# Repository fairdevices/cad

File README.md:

# Faidevices CAD Repository

The Fairdevices project aims to make household appliances repairable. To achieve this, we are currently developing a universal control board for washing machines that is compatible with as many common devices as possible. This repository manages all source files for the washing machine control and documentation.
Status

## Status

The Project is actively maintained and the development is still in a very early stage. Currently, we are focusing on the development of:

- the power supply
- the heating control

## Licensing

The project is licensed under CERN-OHL-S-2.0. All files can be freely used, modified, and republished. The use of the Fairdevices name and logo is reserved for us.

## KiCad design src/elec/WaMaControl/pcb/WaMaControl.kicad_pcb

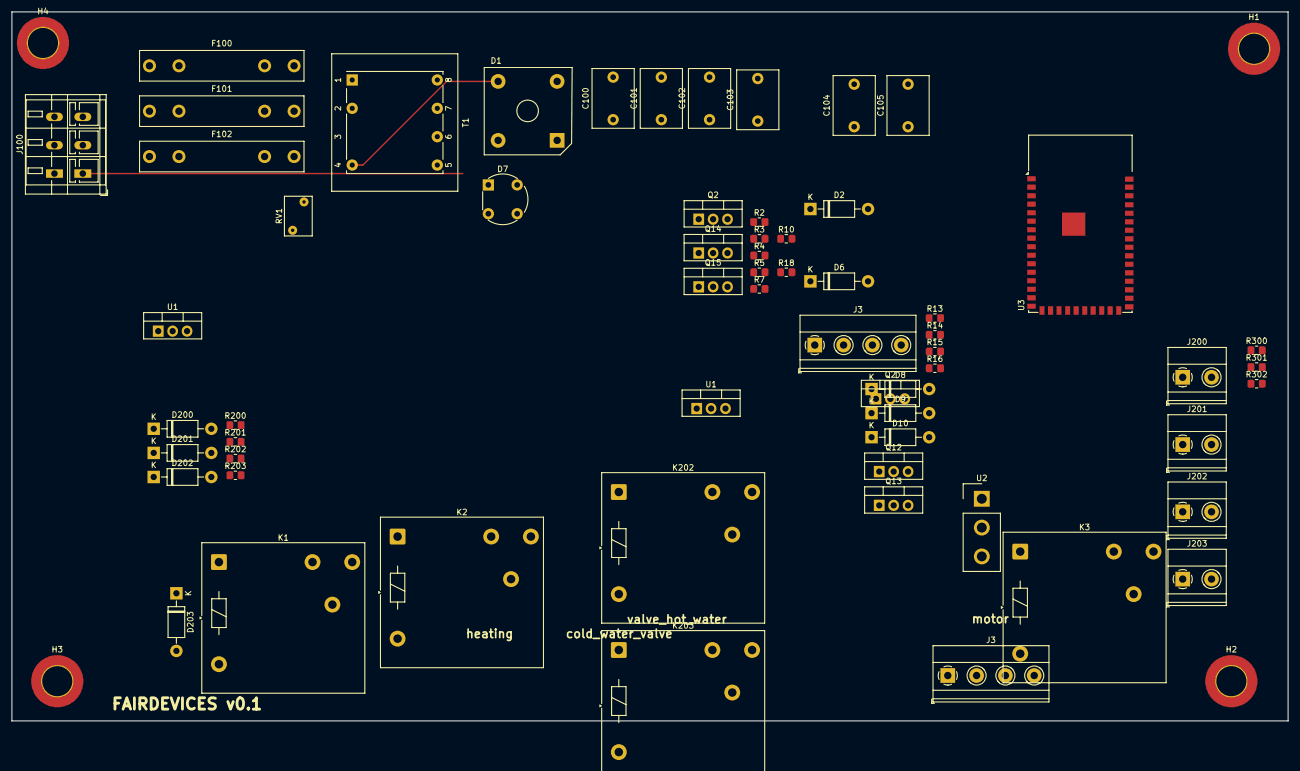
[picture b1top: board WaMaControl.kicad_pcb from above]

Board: 2 copper layers, 225.0 x 125.0 mm, 66 parts (0 on the bottom side), 28 nets.

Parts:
C100, C101, C102, C103, C104, C105: C; C_Rect_L10.3mm_W7.2mm_P7.50mm_MKS4
D1: D_Bridge_+-AA; Diode_Bridge_Vishay_KBPC6
D2, D6, D8, D9, D10, D200, D201, D202, D203: 1N4001; D_DO-41_SOD81_P10.16mm_Horizontal
D7: D_Bridge_+-AA; Diode_Bridge_Round_D8.9mm
F100, F101, F102: Fuse; Fuseholder_Littelfuse_445_030_series_5x25mm
H1, H2, H3, H4: MountingHole; MountingHole_5.3mm_M5_DIN965_Pad_TopBottom
J3, J3#2: Conn_01x04_Female; TerminalBlock_Phoenix_MKDS-1,5-4-5.08_1x04_P5.08mm_Horizont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
J100: Conn_01x03_Female; TerminalBlock_WAGO_236-403_1x03_P5.00mm_45Degree
J200, J201, J202, J203: Conn_01x02_Female; TerminalBlock_Phoenix_MKDS-1,5-2-5.08_1x02_P5.08mm_Horizont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
K1, K2: Relay_SPDT; Relay_SPDT_Finder_40.11
K3, K202, K203: AZ850-x; Relay_SPDT_Finder_40.11
Q2, Q2#2, Q12, Q13, Q14: TIC126; TO-220-3_Vertical
Q15: BT138-600; TO-220-3_Vertical
R2, R3, R4, R5, R7, R10, R13, R14, R15, R16, R18, R200, R201, R202, R203, R300, R301, R302: R_Small; R_0805_2012Metric_Pad1.20x1.40mm_HandSolder
RV1: Varistor; RV_Disc_D7mm_W4.9mm_P5mm
T1: Transformer_1P_1S; Transformer_Breve_TEZ-22x24
U1, U1#2: LF50_TO220; TO-220-3_Vertical
U2: logo_fairdevices; Samtec_HPM-03-01-x-S_Straight_1x03_Pitch5.08mm
U3: ESP32-S2-WROVER

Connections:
+3.3V: C104.1, C105.1, R302.1, U1.3 (VO), U1#2.3 (VO), U3.2 (3V3)
+12V: C100.1, C101.1, C102.1, C103.1, D1.1 (+), D2.1 (K), D6.1 (K), D8.1 (K), D9.1 (K), D10.1 (K), D200.1 (K), D201.1 (K), D202.1 (K), D203.1 (K), K1.A1, K2.A1, U1.1 (VI), U1#2.1 (VI)
AC/L: F100.2, K1.14, K2.14, RV1.1, T1.1 (AA)
AC/N: J3.3, J3#2.3, J100.2, J200.2, J201.2, J202.1, RV1.2, T1.2 (AB)
CNTL-coldh2o: R200.1, U3.10 (IO07)
CNTL-drainpump: R203.1, U3.14 (IO11)
CNTL-heating: R202.1, U3.19 (IO16)
CNTR-warmh2o: R201.1, U3.11 (IO08)
Earth_Protective: C100.2, C101.2, C102.2, C103.2, C104.2, C105.2, D1.2 (-), D7.2 (-), J100.1, R10.1, R16.1, R301.2, U1.2 (GND), U1#2.2 (GND), U3.1 (GND), U3.26 (GND), U3.42 (GND), U3.43 (GND)
unnamed: D7.1 (+), R300.1
unnamed: D200.2 (A), K1.A2
unnamed: D201.2 (A), K2.A2
unnamed: F100.1, F101.1, F102.1, J100.3
unnamed: Q2.2 (A), Q2#2.2 (A)
unnamed: Q2.3 (G), Q2#2.3 (G)
unnamed: Q12.2 (A), Q13.1 (K)
unnamed: Q2.1 (K), Q2#2.1 (K), Q14.2 (A)
unnamed: Q15.2 (A2), R4.2
unnamed: Q15.3 (G), R2.1
Trafo-Sek-1: D1.3, D7.3, D7.4, T1.4 (SB)
coldwatervalve2: J200.1, K1.11
freq: R300.2, R301.1, U3.5 (IO02)
heating1: J202.2, Q14.1 (K), Q15.1 (A1), R2.2, R3.1
hotwatervalve2: J201.1, K2.11
motor1: J3.4, J3#2.4, Q12.1 (K)
motorsensor1: J3.2, J3#2.2
motorsensor2: J3.1, J3#2.1
sens_temperature: R302.2, U3.21 (IO18)

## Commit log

2025-02-01 - migration of development files from 09-11-24
2025-02-01 - migration of development files from 01-02-25
2025-02-22 - Readme updated - License added
2025-02-25 fix / replace tables
